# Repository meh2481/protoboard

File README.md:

# Protoboard
Prototyping board for pi pico development, with some useful features:
- SD card reader
- Test LEDs
- DAC/Speaker
- Pushbuttons
- OLED Display
- 12V->5V buck converter
- USB-C/MicroUSB power in
- Pico pinout protoboard

# Materials
Parts used:
- 1x [I2C OLED Display](https://smile.amazon.com/dp/B09C5K91H7)
- 1x [Pi Pico Breadboard](https://www.adafruit.com/product/5422)
- 1x [3A Fuse](https://smile.amazon.com/dp/B07L8K28N7)
- 2x [Fuse Holder](https://smile.amazon.com/dp/B07SKG4M78)
- 1x [12V Power Supply](https://smile.amazon.com/dp/B01GEA8PQA), optional
- 3x [400-Pin Protoboard](https://smile.amazon.com/dp/B07LFD4LT6)
- 1x [USB-C Connector](https://www.mouser.com/ProductDetail/640-USB4085-GF-A)
- 1x [MicroUSB Connector](https://www.mouser.com/ProductDetail/640-USB3076-30-A)
- 1x [5V Voltage Regulator](https://www.mouser.com/ProductDetail/863-LM2576TV-5G)
- 2x [Shottky Diode](https://www.mouser.com/ProductDetail/583-1N5822-T)
- 1x [100uH Inductor](https://www.mouser.com/ProductDetail/530-HCTI-100-7.0)
- 1x [DC Power Jack](https://www.mouser.com/ProductDetail/490-PJ-102AH)
- 1x [MicroSD connector](https://www.digikey.com/en/products/detail/molex/1040310811/2370379)
- 1x [Speaker](https://www.digikey.com/en/products/detail/db-unlimited/SM231508-1/9990601)
- 5x [2x2 2.54mm Female Pin Header](https://www.digikey.com/en/products/detail/sullins-connector-solutions/PPTC022LFBN-RC/810209)
- 8x M2x8 screws
- 4x M2.5x4-ish screws
- 1x 1x4 2.54mm Female Pin Header
- 1x 1x8 2.54mm Female Pin Header
- 4x 6mm Push Buttons
- Various resistors/capacitors/LEDs/switches

# Improvements
This project is complete, but if you make it you'll probably want to make some changes.
- Power LED resistor should go to GND, not GND_SWITCHED. That way LED is off when switch is off.
- Protoboards seem off-center? Probably not measured correctly.
- Smaller inductor; current one is probably overkill.
- Buck converter on right side of board, not left (or pico protoboard on right side) for easier wiring when prototyping.
- Amp like [this one](https://www.adafruit.com/product/2130) for speaker works really well if you can fit it on the board.
- 5V->3V3 stepdown might be a good idea if you don't want to be tied to the pico's power supply.
- Better PCB labels/warnings against using 3V3 on SD card/etc.

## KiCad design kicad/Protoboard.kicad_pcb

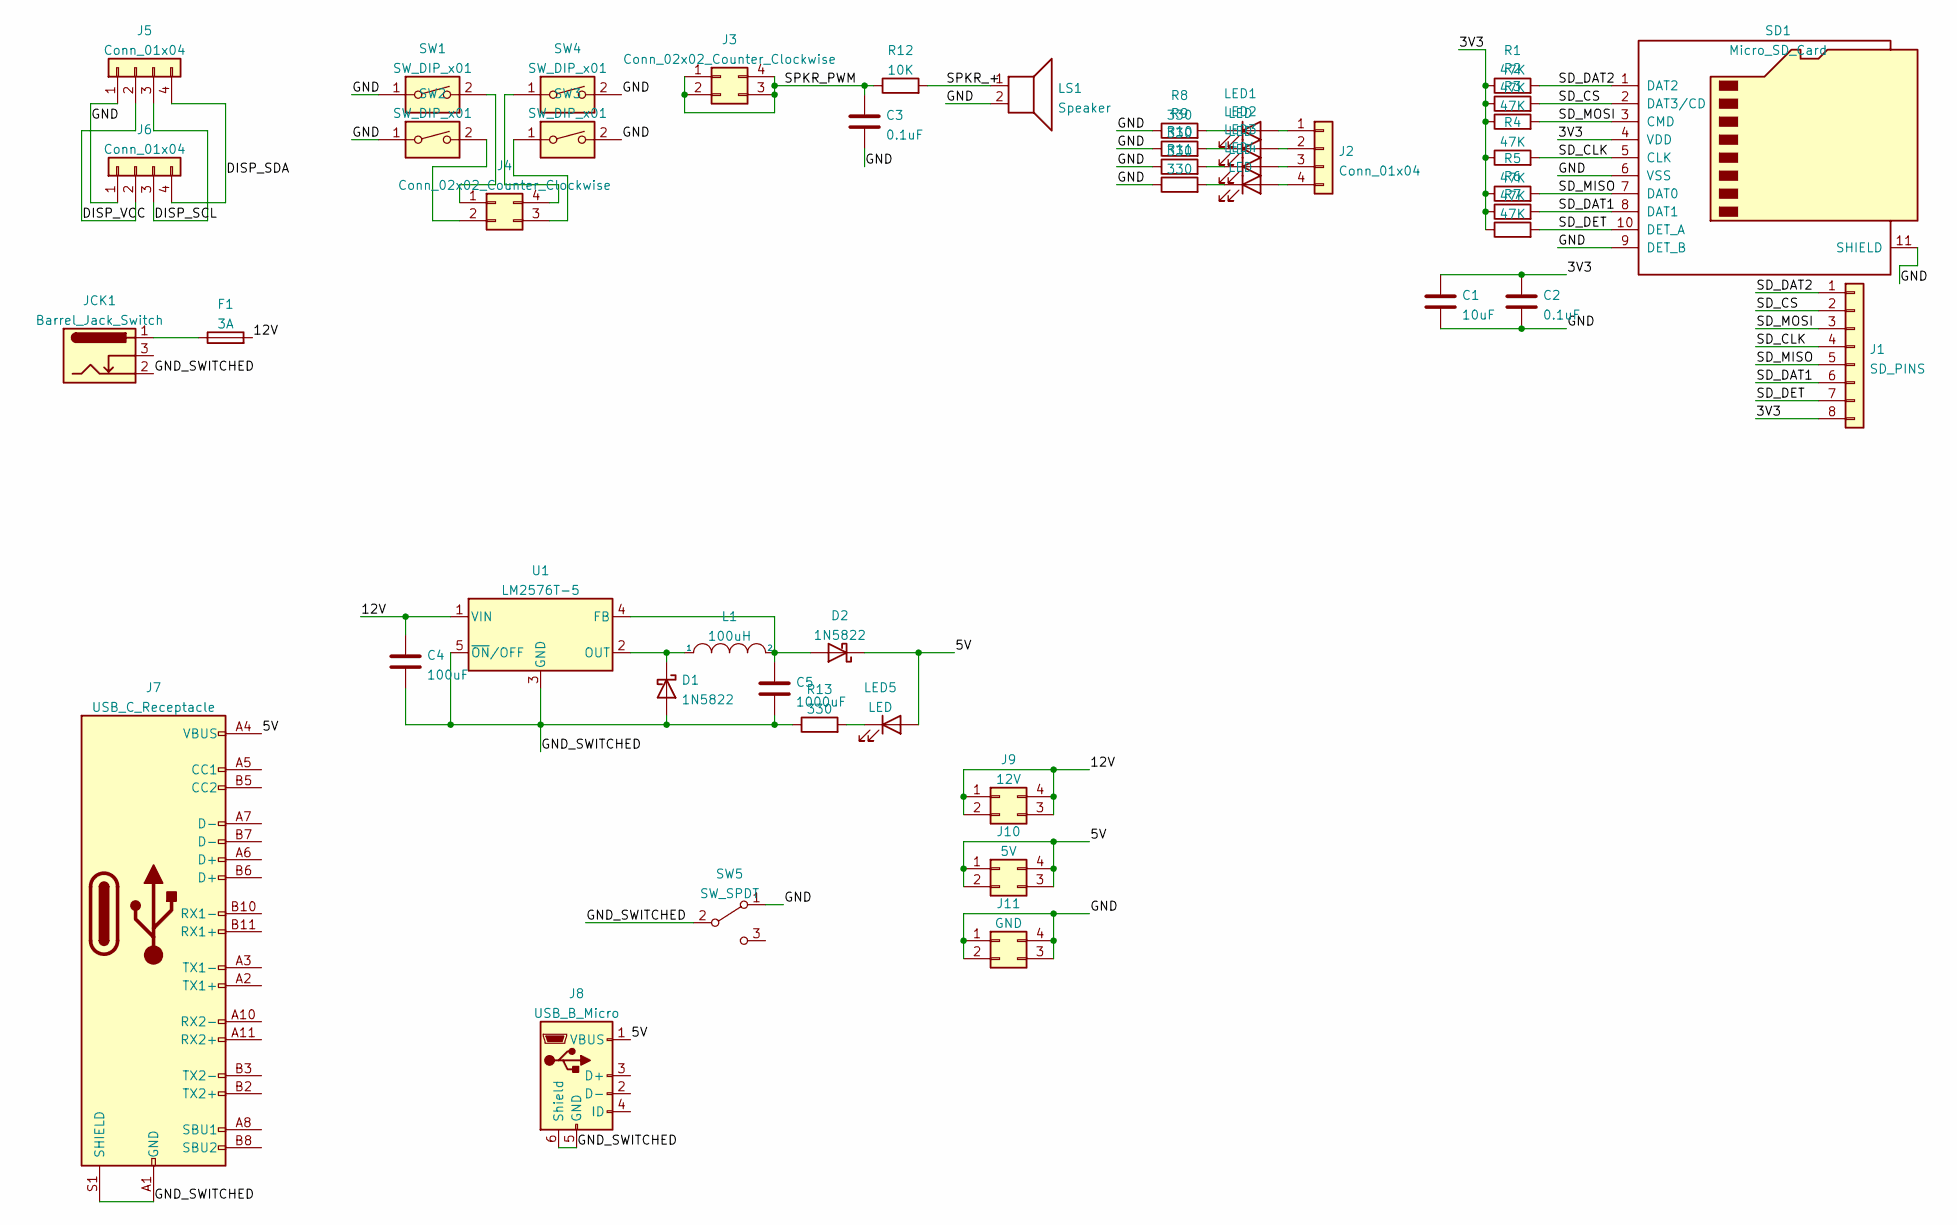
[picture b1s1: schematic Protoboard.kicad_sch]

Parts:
C1: 10uF; C_Disc_D5.1mm_W3.2mm_P5.00mm
C2, C3: 0.1uF; C_Disc_D5.1mm_W3.2mm_P5.00mm
C4: 100uF; CP_Radial_D8.0mm_P3.50mm
C5: 1000uF; CP_Radial_D10.0mm_P5.00mm
D1, D2: 1N5822; D_DO-201AD_P12.70mm_Horizontal
F1: 3A; FuseHolder_3.5x9.75mm
J1: SD_PINS; PinSocket_1x08_P2.54mm_Vertical
J2, J6: Conn_01x04; PinSocket_1x04_P2.54mm_Vertical
J3, J4: Conn_02x02_Counter_Clockwise; PinSocket_2x02_P2.54mm_Vertical
J5: Conn_01x04; PinHeader_1x04_P2.54mm_Vertical
J7: USB_C_Receptacle; USB_C_Receptacle_GCT_USB4085
J8: USB_B_Micro; USB_Micro-B_GCT_USB3076-30-A
J9: 12V; PinSocket_2x02_P2.54mm_Vertical
J10: 5V; PinSocket_2x02_P2.54mm_Vertical
J11: GND; PinSocket_2x02_P2.54mm_Vertical
JCK1: Barrel_Jack_Switch; BarrelJack_CUI_PJ-102AH_Horizontal
L1: 100uH; L_Toroid_Vertical_L28.6mm_W14.3mm_P11.43mm_Bourns_5700
LED1, LED2, LED3, LED4, LED5: LED; LED_D5.0mm
LS1: Speaker; Buzzer_D14mm_H7mm_P10mm
R1, R2, R3, R4, R5, R6, R7: 47K; R_Axial_DIN0207_L6.3mm_D2.5mm_P2.54mm_Vertical
R8, R9, R10, R11, R13: 330; R_Axial_DIN0207_L6.3mm_D2.5mm_P10.16mm_Horizontal
R12: 10K; R_Axial_DIN0309_L9.0mm_D3.2mm_P12.70mm_Horizontal
SD1: Micro_SD_Card; microSD_HC_Molex_104031-0811
SW1, SW2, SW3, SW4: SW_DIP_x01; SW_PUSH_6mm_H7.3mm
SW5: SW_SPDT; PinHeader_1x03_P2.54mm_Vertical
U1: LM2576T-5; TO-220-5_P3.4x3.7mm_StaggerOdd_Lead3.8mm_Vertical

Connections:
/3V3: C1.1, C2.1, J1.8, R1.1, R2.1, R3.1, R4.1, R5.1, R6.1, R7.1, SD1.4 (VDD)
/5V: D2.1 (K), J7.A4 (VBUS), J7.A9 (VBUS), J7.B4 (VBUS), J7.B9 (VBUS), J8.1 (VBUS), J10.1, J10.2, J10.3, J10.4, LED5.2 (A)
/12V: C4.1, F1.2, J9.1, J9.2, J9.3, J9.4, U1.1 (VIN)
/DISP_SCL: J5.3, J6.3
/DISP_SDA: J5.4, J6.4
/DISP_VCC: J5.2, J6.2
/GND: C1.2, C2.2, C3.2, J5.1, J6.1, J11.1, J11.2, J11.3, J11.4, LS1.2, R8.1, R9.1, R10.1, R11.1, SD1.6 (VSS), SD1.9 (DET_B), SD1.11 (SHIELD), SW1.1, SW2.1, SW3.2, SW4.2, SW5.1 (A)
/GND_SWITCHED: C4.2, C5.2, D1.2 (A), J7.A1 (GND), J7.A12 (GND), J7.B1 (GND), J7.B12 (GND), J7.S1 (SHIELD), J8.5 (GND), J8.6 (Shield), JCK1.2, R13.1, SW5.2 (B), U1.3 (GND), U1.5 (~ON/OFF)
/SD_CLK: J1.4, R4.2, SD1.5 (CLK)
/SD_CS: J1.2, R2.2, SD1.2 (DAT3/CD)
/SD_DAT1: J1.6, R6.2, SD1.8 (DAT1)
/SD_DAT2: J1.1, R1.2, SD1.1 (DAT2)
/SD_DET: J1.7, R7.2, SD1.10 (DET_A)
/SD_MISO: J1.5, R5.2, SD1.7 (DAT0)
/SD_MOSI: J1.3, R3.2, SD1.3 (CMD)
/SPKR_+: LS1.1, R12.2
/SPKR_PWM: C3.1, J3.1, J3.2, J3.3, J3.4, R12.1
unnamed: D1.1 (K), L1.1, U1.2 (OUT)
unnamed: F1.1, JCK1.1
unnamed: J2.1, LED1.2 (A)
unnamed: J2.2, LED2.2 (A)
unnamed: J2.3, LED3.2 (A)
unnamed: J2.4, LED4.2 (A)
unnamed: J4.1, SW1.2
unnamed: J4.2, SW2.2
unnamed: J4.3, SW3.1
unnamed: J4.4, SW4.1
unnamed: C5.1, D2.2 (A), L1.2, U1.4 (FB)
unnamed: LED1.1 (K), R8.2
unnamed: LED2.1 (K), R9.2
unnamed: LED3.1 (K), R10.2
unnamed: LED4.1 (K), R11.2
unnamed: LED5.1 (K), R13.2

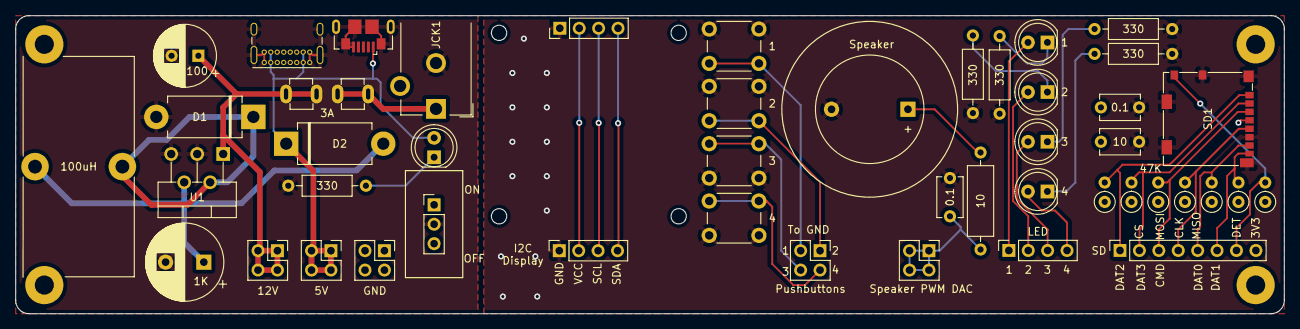
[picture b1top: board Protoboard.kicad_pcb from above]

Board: 2 copper layers, 166.0 x 39.0 mm, 47 parts (0 on the bottom side), 33 nets.

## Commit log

2022-05-14 Add README
2022-05-14 Complete BOM
2022-05-15 Add improvements/image to readme
